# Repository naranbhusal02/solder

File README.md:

# Description:
This is a very compact PCB that is designed to produce a sound and glow in complete darkness by using a photoresistor hooked up to a transistor and the sound can be turned off using a push switch.
# Parts list:
Battery x1 Push Switch x2 Buzzer x1 Resistor x7 LED x5 NPN-transitor x1 Photoresistor x1
# Some Glimpses:

# Slack ID:  
naranbhusal02

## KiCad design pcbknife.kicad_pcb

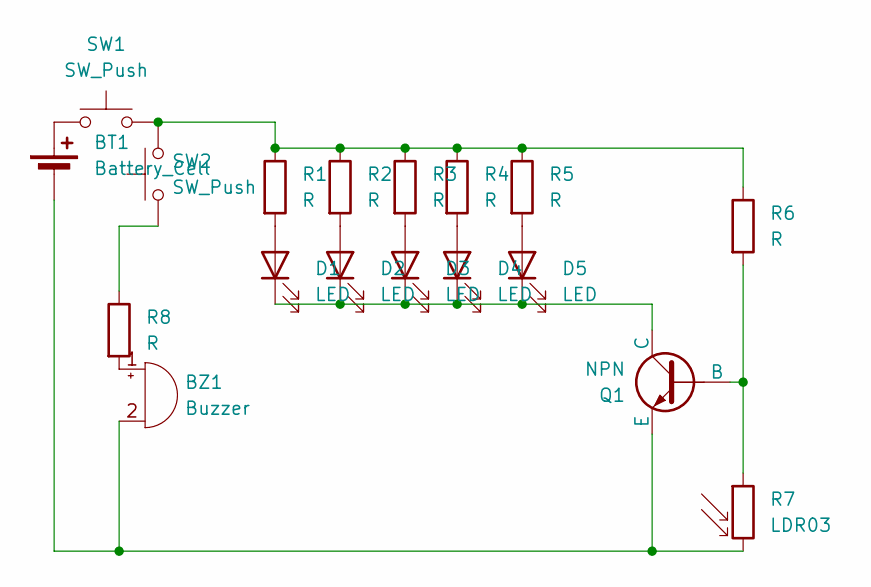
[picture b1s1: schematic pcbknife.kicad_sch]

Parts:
BT1: Battery_Cell; BatteryHolder_Keystone_3034_1x20mm
BZ1: Buzzer; MagneticBuzzer_ProSignal_ABI-009-RC
D1, D2, D3, D4, D5: LED; LED_D5.0mm
Q1: NPN; TO-92L_HandSolder
R1, R2, R3, R4, R5, R6, R8: R; R_Axial_DIN0207_L6.3mm_D2.5mm_P7.62mm_Horizontal
R7: LDR03; R_LDR_5.1x4.3mm_P3.4mm_Vertical
SW1, SW2: SW_Push; SW_PUSH_6mm

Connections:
unnamed: BT1.1 (+), SW1.1
unnamed: BT1.2 (-), BZ1.2 (-), Q1.3 (E), R7.2
unnamed: BZ1.1 (+), R8.2
unnamed: D1.2 (A), R1.2
unnamed: D1.1 (K), D2.1 (K), D3.1 (K), D4.1 (K), D5.1 (K), Q1.1 (C)
unnamed: D2.2 (A), R2.2
unnamed: D3.2 (A), R3.2
unnamed: D4.2 (A), R4.2
unnamed: D5.2 (A), R5.2
unnamed: Q1.2 (B), R6.2, R7.1
unnamed: R1.1, R2.1, R3.1, R4.1, R5.1, R6.1, SW1.2, SW2.2
unnamed: R8.1, SW2.1

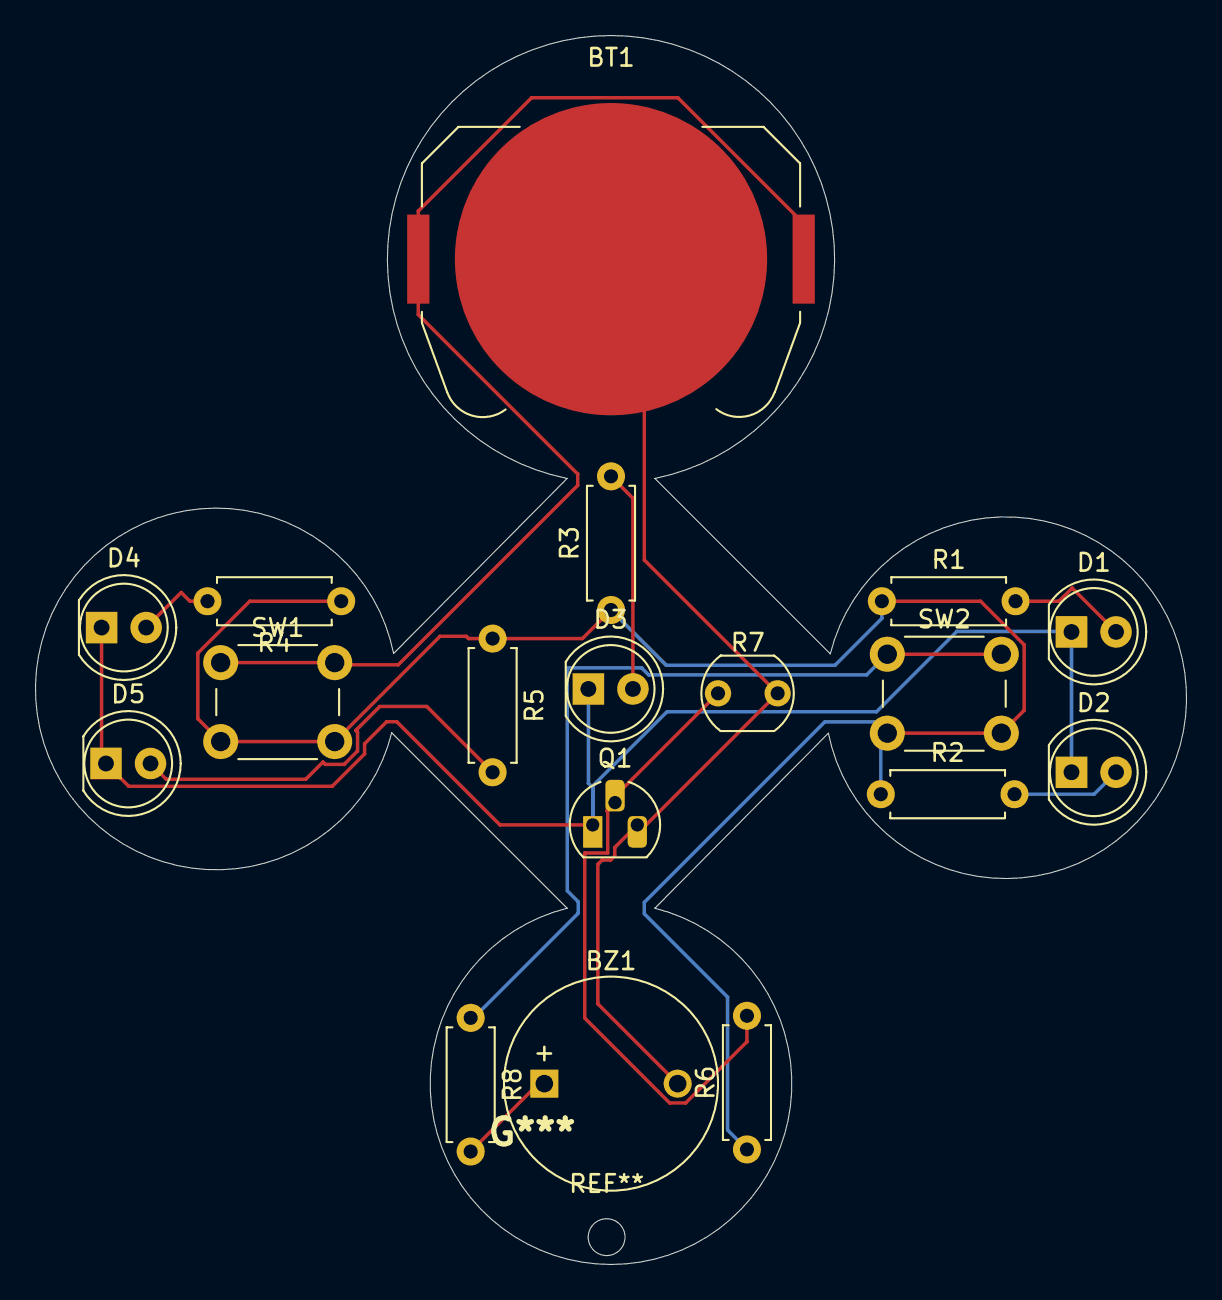
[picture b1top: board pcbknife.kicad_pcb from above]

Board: 2 copper layers, 65.6 x 70.1 mm, 18 parts (0 on the bottom side), 12 nets.

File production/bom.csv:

Designator,Footprint,Quantity,Value,LCSC Part #
BT1,BatteryHolder_Keystone_3034_1x20mm,1,Battery_Cell,
BZ1,MagneticBuzzer_ProSignal_ABI-009-RC,1,Buzzer,
"D1, D2, D3, D4, D5",LED_D5.0mm,5,LED,
Q1,TO-92L_HandSolder,1,NPN,
"R1, R2, R3, R4, R5, R6, R8",R_Axial_DIN0207_L6.3mm_D2.5mm_P7.62mm_Horizontal,7,R,
R7,R_LDR_5.1x4.3mm_P3.4mm_Vertical,1,LDR03,
"SW1, SW2",SW_PUSH_6mm,2,SW_Push,
